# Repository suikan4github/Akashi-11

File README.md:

# Akashi-11
Prototype of the EL-210 mod 

## Description

This board is prototype of the [EL-210-MOD](https://github.com/suikan4github/EL-210-MOD) board. Akashi-11 is designed to mount on the 
[Nucleo G0B1RE](https://www.st.com/ja/evaluation-tools/nucleo-g0b1re.html) board and 
to be connected with the  [Akashi-10 board](https://github.com/suikan4github/Akashi-10) in EL-210. 

The battery power is supplied from the EL-210 through a ribbon cable. This power is 
boosted on the board to be a 3.3V. And supplied to Nucleo through the pin 12 and 16 of 
the CN7. To avoid an accident, the bridge SB1 on the Nucleo G0B1RE must be cut. 

Also, the NRST signal from STLINK must be cut. 

Signal assignment of Nucleo is as following : 

| Signal | GPIO Pin |
|-|-|
| KC0 | PA10 |
| KC1 | PB3 |
| KC2 | PB5 |
| KR8 | PA5 |
| KR7 | PA6 |
| KR6 | PC1 |
| KR5 | PB0 |
| KR4 | PC7 |
| KR3 | PB2 |
| KR2 | PB6 |
| KR1 | PB14 |
| KR0 | PB4 |
| SPI1_MOSI | PA12 |
| SPI1_SCK | PD8 |
| LOAD | PC10 |
| BLANK | PC12 |
| TIM1_CH1 | PA8 |
| TIM1_CH1N | PA7 |
| TIM1_CH2 | PA9 |
| EN24 | PC11 |
| STATUS | PD2 |

Refer the [EL-210-MOD](https://github.com/suikan4github/EL-210-MOD) project for details of the circuit design. 

# Gallery

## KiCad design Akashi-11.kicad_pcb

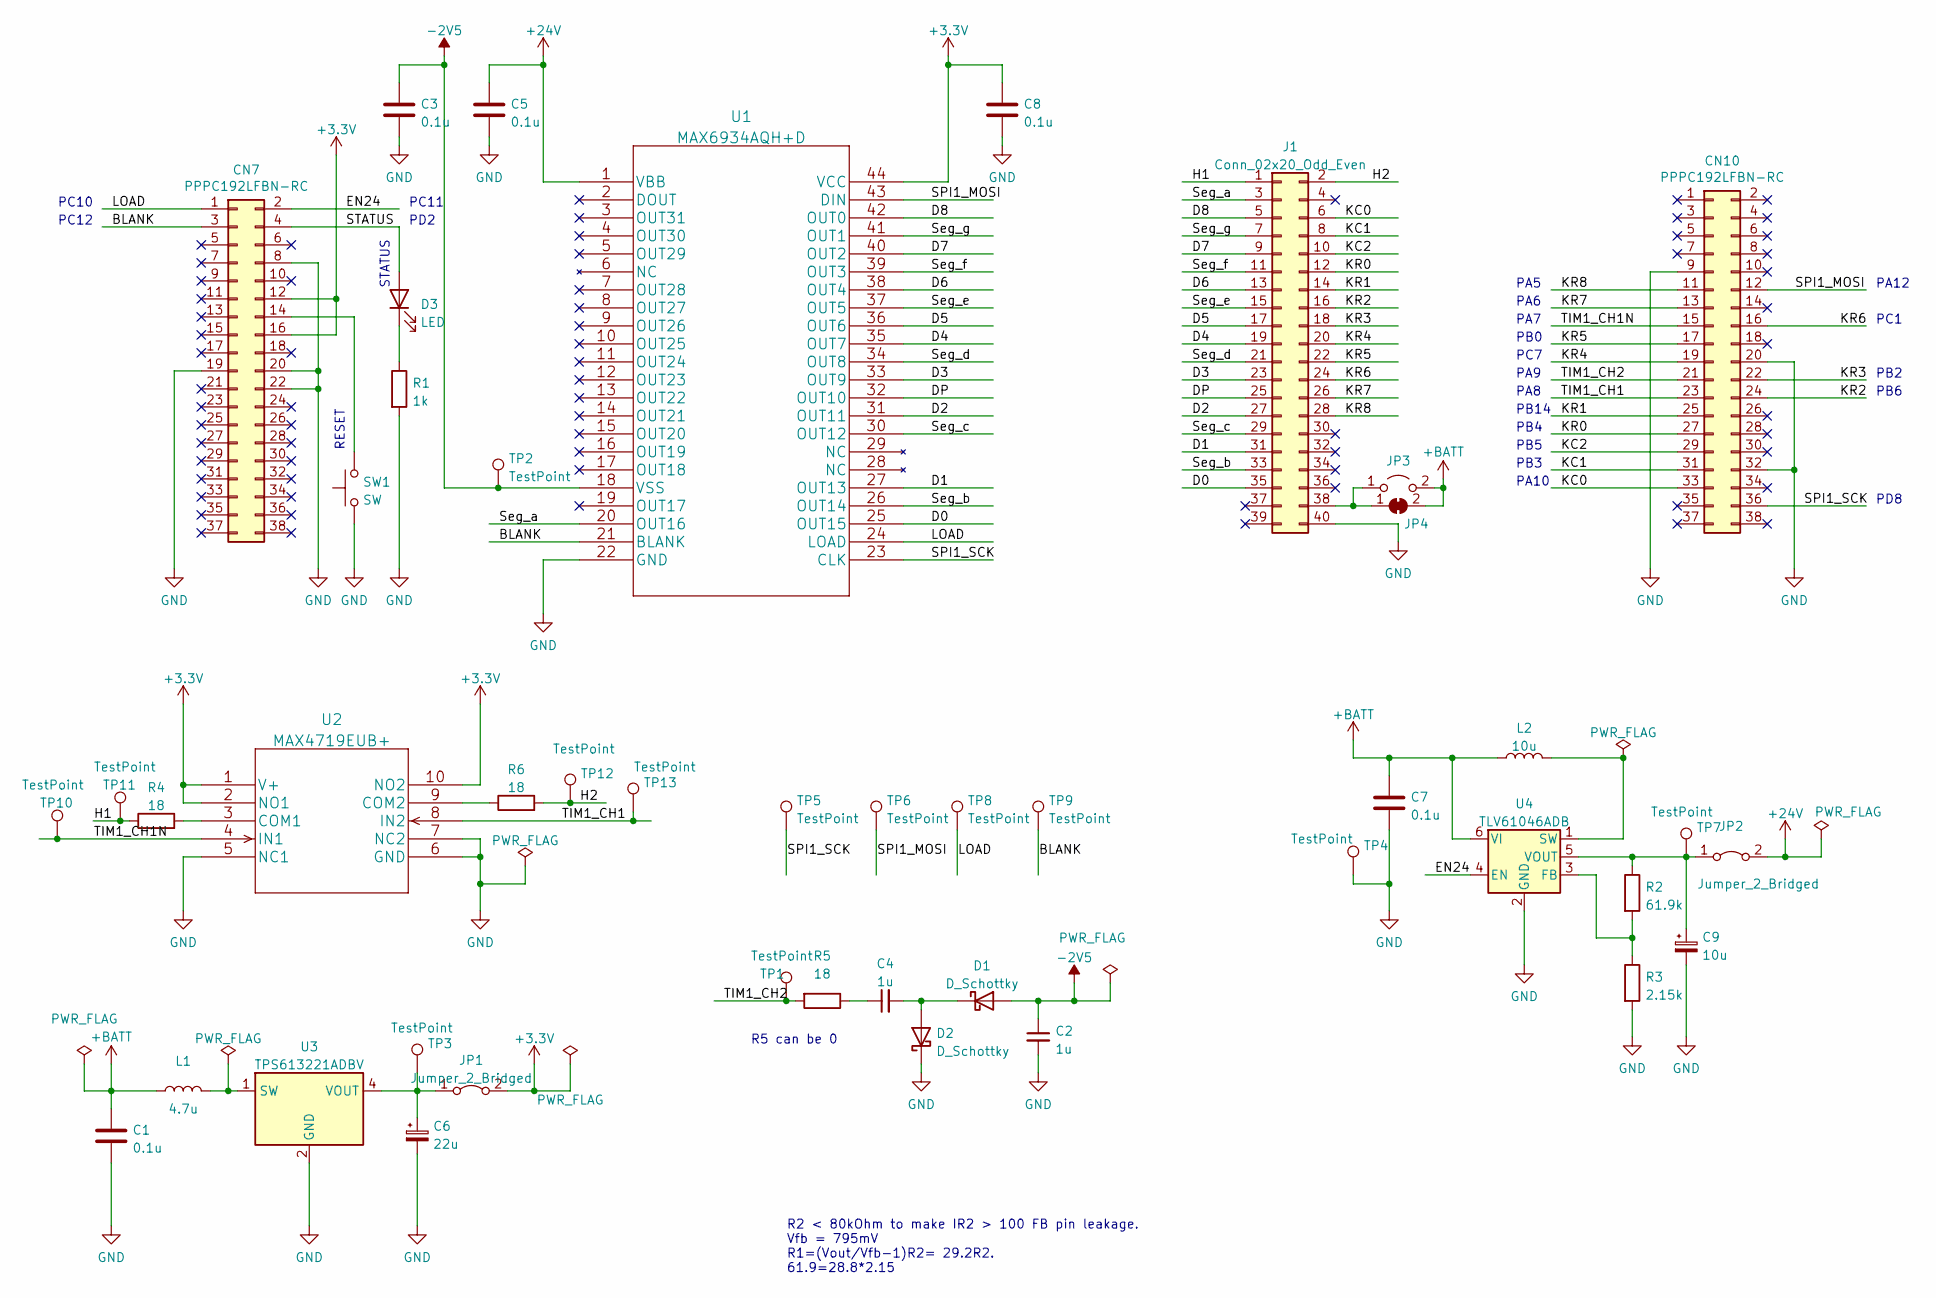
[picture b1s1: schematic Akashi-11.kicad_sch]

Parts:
C1, C3, C5, C7, C8: 0.1u; C_0603_1608Metric_Pad1.08x0.95mm_HandSolder
C2, C4: 1u; C_0603_1608Metric_Pad1.08x0.95mm_HandSolder
C6: 22u; CP_Elec_6.3x3
C9: 10u; CP_Elec_4x3.9
CN7, CN10: PPPC192LFBN-RC; PinSocket_2x19_P2.54mm_Vertical
D1, D2: D_Schottky; C_0603_1608Metric_Pad1.08x0.95mm_HandSolder
D3: LED; LED_D4.0mm
J1: Conn_02x20_Odd_Even; PinHeader_2x20_P2.54mm_Vertical
JP1, JP2: Jumper_2_Bridged; SolderJumper-2_P1.3mm_Bridged_RoundedPad1.0x1.5mm
JP3: Jumper_2_Open; PinHeader_1x02_P2.54mm_Vertical
JP4: SolderJumper_2_Bridged; SolderJumper-2_P1.3mm_Bridged_RoundedPad1.0x1.5mm
L1: 4.7u; LQH5BPN100M38L
L2: 10u; LQH5BPN100M38L
R1: 1k; C_0603_1608Metric_Pad1.08x0.95mm_HandSolder
R2: 61.9k; C_0603_1608Metric_Pad1.08x0.95mm_HandSolder
R3: 2.15k; C_0603_1608Metric_Pad1.08x0.95mm_HandSolder
R4, R5, R6: 18; C_0603_1608Metric_Pad1.08x0.95mm_HandSolder
SW1: SW; SW_TH_Tactile_Omron_B3F-10xx
TP1, TP2, TP3, TP4, TP5, TP6, TP7, TP8, TP9, TP10, TP11, TP12, TP13: TestPoint; TestPoint_Loop_D1.80mm_Drill1.0mm_Beaded
U1: MAX6934AQH+D; PLCC-44_THT-Socket
U2: MAX4719EUB+; MAX4719EUB
U3: TPS613221ADBV; SOT-23-5
U4: TLV61046ADB; SOT-23-6

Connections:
+3V3: C8.1, CN7.12, CN7.16, JP1.2 (B), U1.44 (VCC), U2.1 (V+), U2.2 (NO1), U2.10 (NO2)
+24V: C5.1, JP2.2 (B), U1.1 (VBB)
+BATT: C1.1, C7.1, JP3.2 (B), JP4.2 (B), L1.1, L2.1, U4.6 (VI)
-2V5: C2.1, C3.1, D1.2 (A), TP2.1, U1.18 (VSS)
/BLANK: CN7.3, TP9.1, U1.21 (BLANK)
/D0: J1.35, U1.25 (OUT15)
/D1: J1.31, U1.27 (OUT13)
/D2: J1.27, U1.31 (OUT11)
/D3: J1.23, U1.33 (OUT9)
/D4: J1.19, U1.35 (OUT7)
/D5: J1.17, U1.36 (OUT6)
/D6: J1.13, U1.38 (OUT4)
/D7: J1.9, U1.40 (OUT2)
/D8: J1.5, U1.42 (OUT0)
/DP: J1.25, U1.32 (OUT10)
/EN24: CN7.2, U4.4 (EN)
/H1: J1.1, R4.1, TP11.1
/H2: J1.2, R6.2, TP12.1
/KC0: CN10.33, J1.6
/KC1: CN10.31, J1.8
/KC2: CN10.29, J1.10
/KR0: CN10.27, J1.12
/KR1: CN10.25, J1.14
/KR2: CN10.24, J1.16
/KR3: CN10.22, J1.18
/KR4: CN10.19, J1.20
/KR5: CN10.17, J1.22
/KR6: CN10.16, J1.24
/KR7: CN10.13, J1.26
/KR8: CN10.11, J1.28
/LOAD: CN7.1, TP8.1, U1.24 (LOAD)
/SPI1_MOSI: CN10.12, TP6.1, U1.43 (DIN)
/SPI1_SCK: CN10.36, TP5.1, U1.23 (CLK)
/STATUS: CN7.4, D3.2 (A)
/Seg_a: J1.3, U1.20 (OUT16)
/Seg_b: J1.33, U1.26 (OUT14)
/Seg_c: J1.29, U1.30 (OUT12)
/Seg_d: J1.21, U1.34 (OUT8)
/Seg_e: J1.15, U1.37 (OUT5)
/Seg_f: J1.11, U1.39 (OUT3)
/Seg_g: J1.7, U1.41 (OUT1)
/TIM1_CH1: CN10.23, TP13.1, U2.8 (IN2)
/TIM1_CH1N: CN10.15, TP10.1, U2.4 (IN1)
/TIM1_CH2: CN10.21, R5.2, TP1.1
GND: C1.2, C2.2, C3.2, C5.2, C6.2, C7.2, C8.2, C9.2, CN7.8, CN7.19, CN7.20, CN7.22, CN10.9, CN10.20, CN10.32, D2.1 (K), J1.40, R1.2, R3.2, SW1.1 (A), SW1.2 (A), TP4.1, U1.22 (GND), U2.5 (NC1), U2.6 (GND), U2.7 (NC2), U3.2 (GND), U4.2 (GND)
unnamed: C4.1, R5.1
unnamed: C4.2, D1.1 (K), D2.2 (A)
unnamed: C6.1, JP1.1 (A), TP3.1, U3.4 (VOUT)
unnamed: C9.1, JP2.1 (A), R2.1, TP7.1, U4.5 (VOUT)
unnamed: CN7.14, SW1.3 (B), SW1.4 (B)
unnamed: D3.1 (K), R1.1
unnamed: J1.38, JP3.1 (A), JP4.1 (A)
unnamed: L1.2, U3.1 (SW)
unnamed: L2.2, U4.1 (SW)
unnamed: R2.2, R3.1, U4.3 (FB)
unnamed: R4.2, U2.3 (COM1)
unnamed: R6.1, U2.9 (COM2)

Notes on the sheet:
PB6
PD8
RESET
PA9
STATUS
R5 can be 0
PC1
PB2
R2 < 80kOhm to make IR2 > 100 FB pin leakage. Vfb = 795mV R1=(Vout/Vfb-1)R2= 29.2R2. 61.9=28.8*2.15
PC10
PA5
PB4
PB5
PB14
PA6
PB3
PC11
PC12
PB0
PD2
PA10
PA8
PC7
PA12
PA7

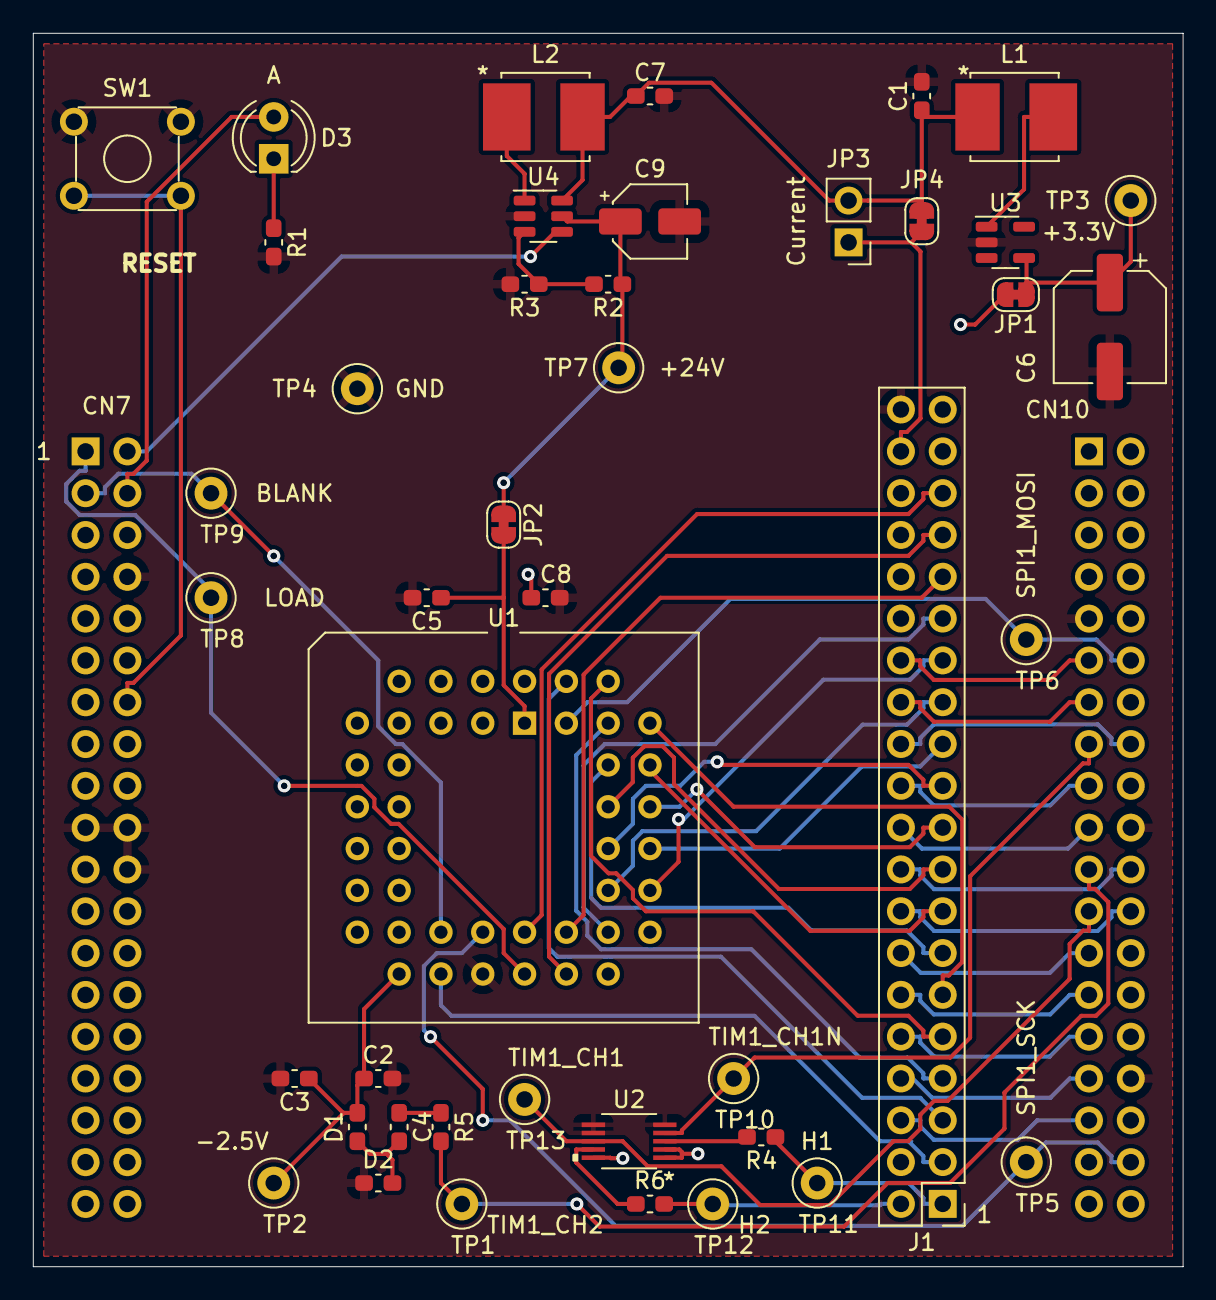
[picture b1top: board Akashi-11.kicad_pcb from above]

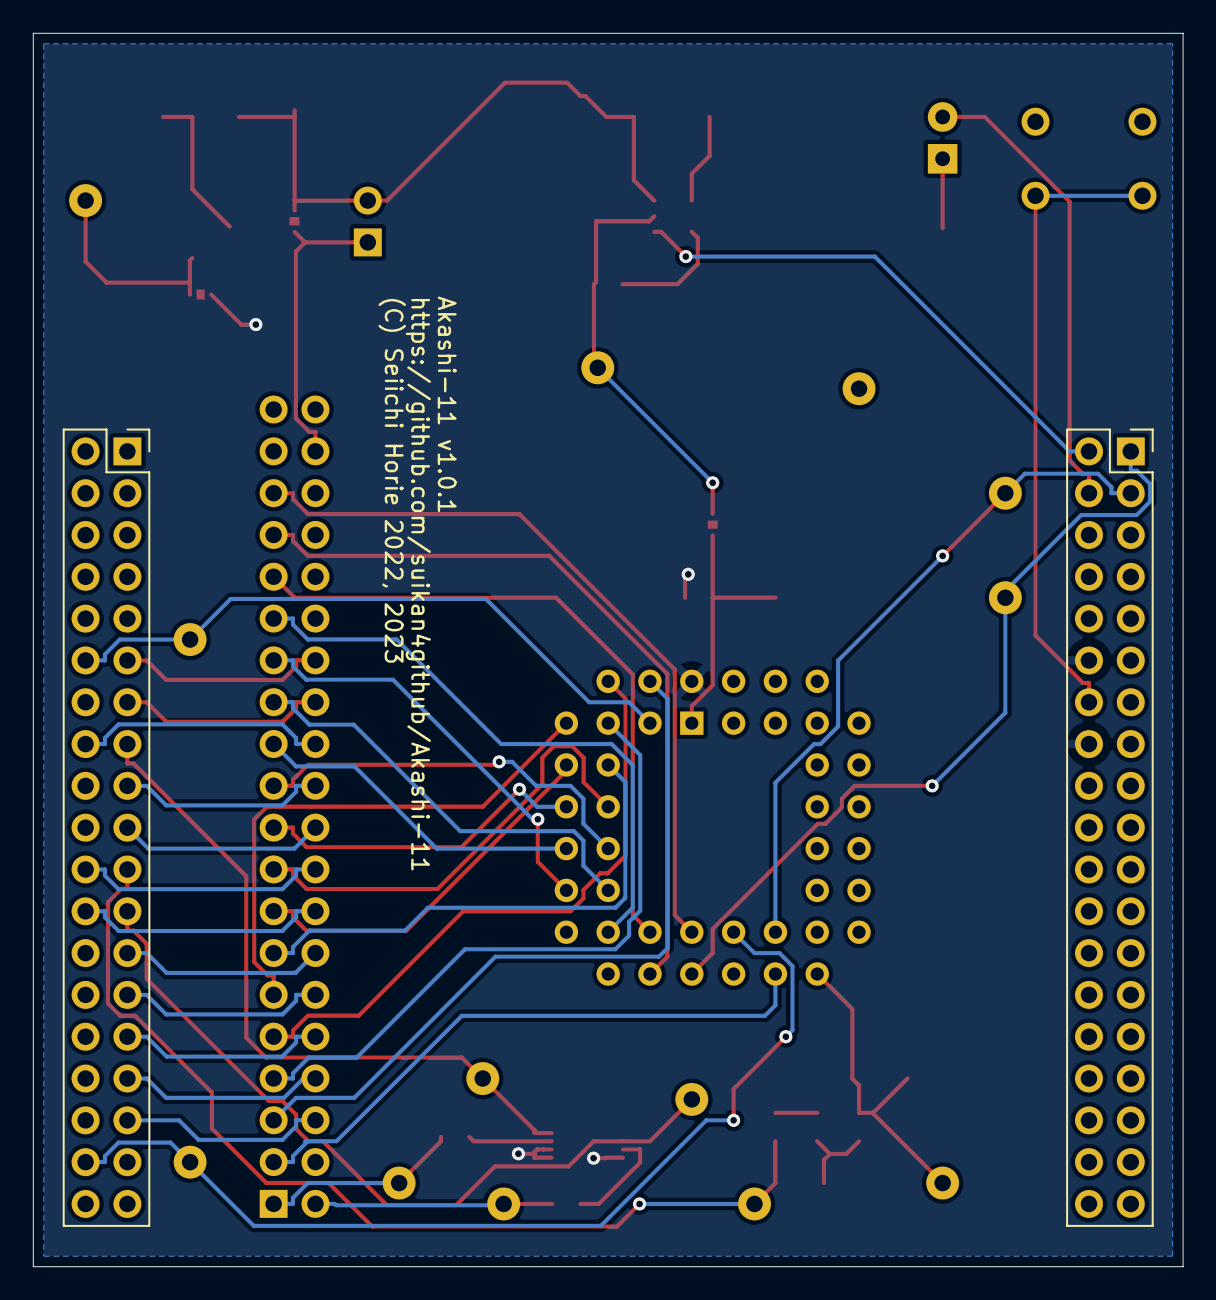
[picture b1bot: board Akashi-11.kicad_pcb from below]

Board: 2 copper layers, 69.9 x 74.9 mm, 45 parts (2 on the bottom side), 57 nets.

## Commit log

2022-10-10 Place empty schematics and board design.
2022-10-23 Rough schematics drawing.
2022-10-23 Add bypass capacitor to -2.5V of the VFD driver.
    Schematics layout is refined.
2022-11-06 ERC finished
2022-11-06 Initial layout of PCB.
2022-11-12 Routing finished
2022-11-12 Add EN24 signal and description of README
2022-11-12 Refine the README
2022-11-14 Layout of schematics is refined.
    Added schematics PDF.
2022-11-23 Layout refined.
    Footprint of L is updated for hand soldering.
    Electric Capacitor foot print is now same with EL-210-MOD.
    Heater resiters are now same withe EL-210-MOD.
2022-11-27 Add current measurment point
2022-11-27 Add PDF schematics.
2022-12-03 Changed from Nucleo to RPi Pico
2022-12-10 Revert "Changed from Nucleo to RPi Pico"
    This reverts commit 16e9e4a1a83ee259be72a8795d021f70ac3e2adc.
2022-12-11 Gerber file generated
2023-01-09 Change signal name from TIM2_CH1 to TIM1_CH2
    Fixed typo. The layout is not changed.
    The sylkscreen of the singal is still wrong.
2023-01-11 Modified schematics and silk.
    - KEY matrix signal name is changed.
    -- Including bug fix of the row order.
    - R5 is changed to small resiter to fix the to small voltage.
    Gerber re-generated. Schematics re-generated in PDF.
2023-01-11 Added image, fixed table.
    Added image to README.
    Also, fixed table on the README. The key matrix signals are renamed.
2023-01-21 README updated

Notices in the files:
parts and their libraries:
Copyright 2021 Accelerated Designs. All rights reserved.
